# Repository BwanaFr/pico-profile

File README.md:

# pico-profile

This project goal is to emulate a Profile/Widget hard disk.
My ultimate goal is to be able to use this circuit with my Apple Lisa computer.

It's a work in progress and not yet ready for production.

## Demo
A short video showing the project in action is available on [Youtube](https://youtu.be/dQjzqoluw7A)

## Licensing
The final license of this project is not yet determined.
No commercial usage of this project can be made.

## TODO:
- Improve how Apple resets the MCU
- Add buttons to choose the disk image to use
- ~~Add more silkscreen information (power supply polarity...)~~
- Design a 3D printed enclosure
- ~~Fix the 74L280 footprint on PCB~~
- Make a through hole PCB version
- Test it with an Apple III

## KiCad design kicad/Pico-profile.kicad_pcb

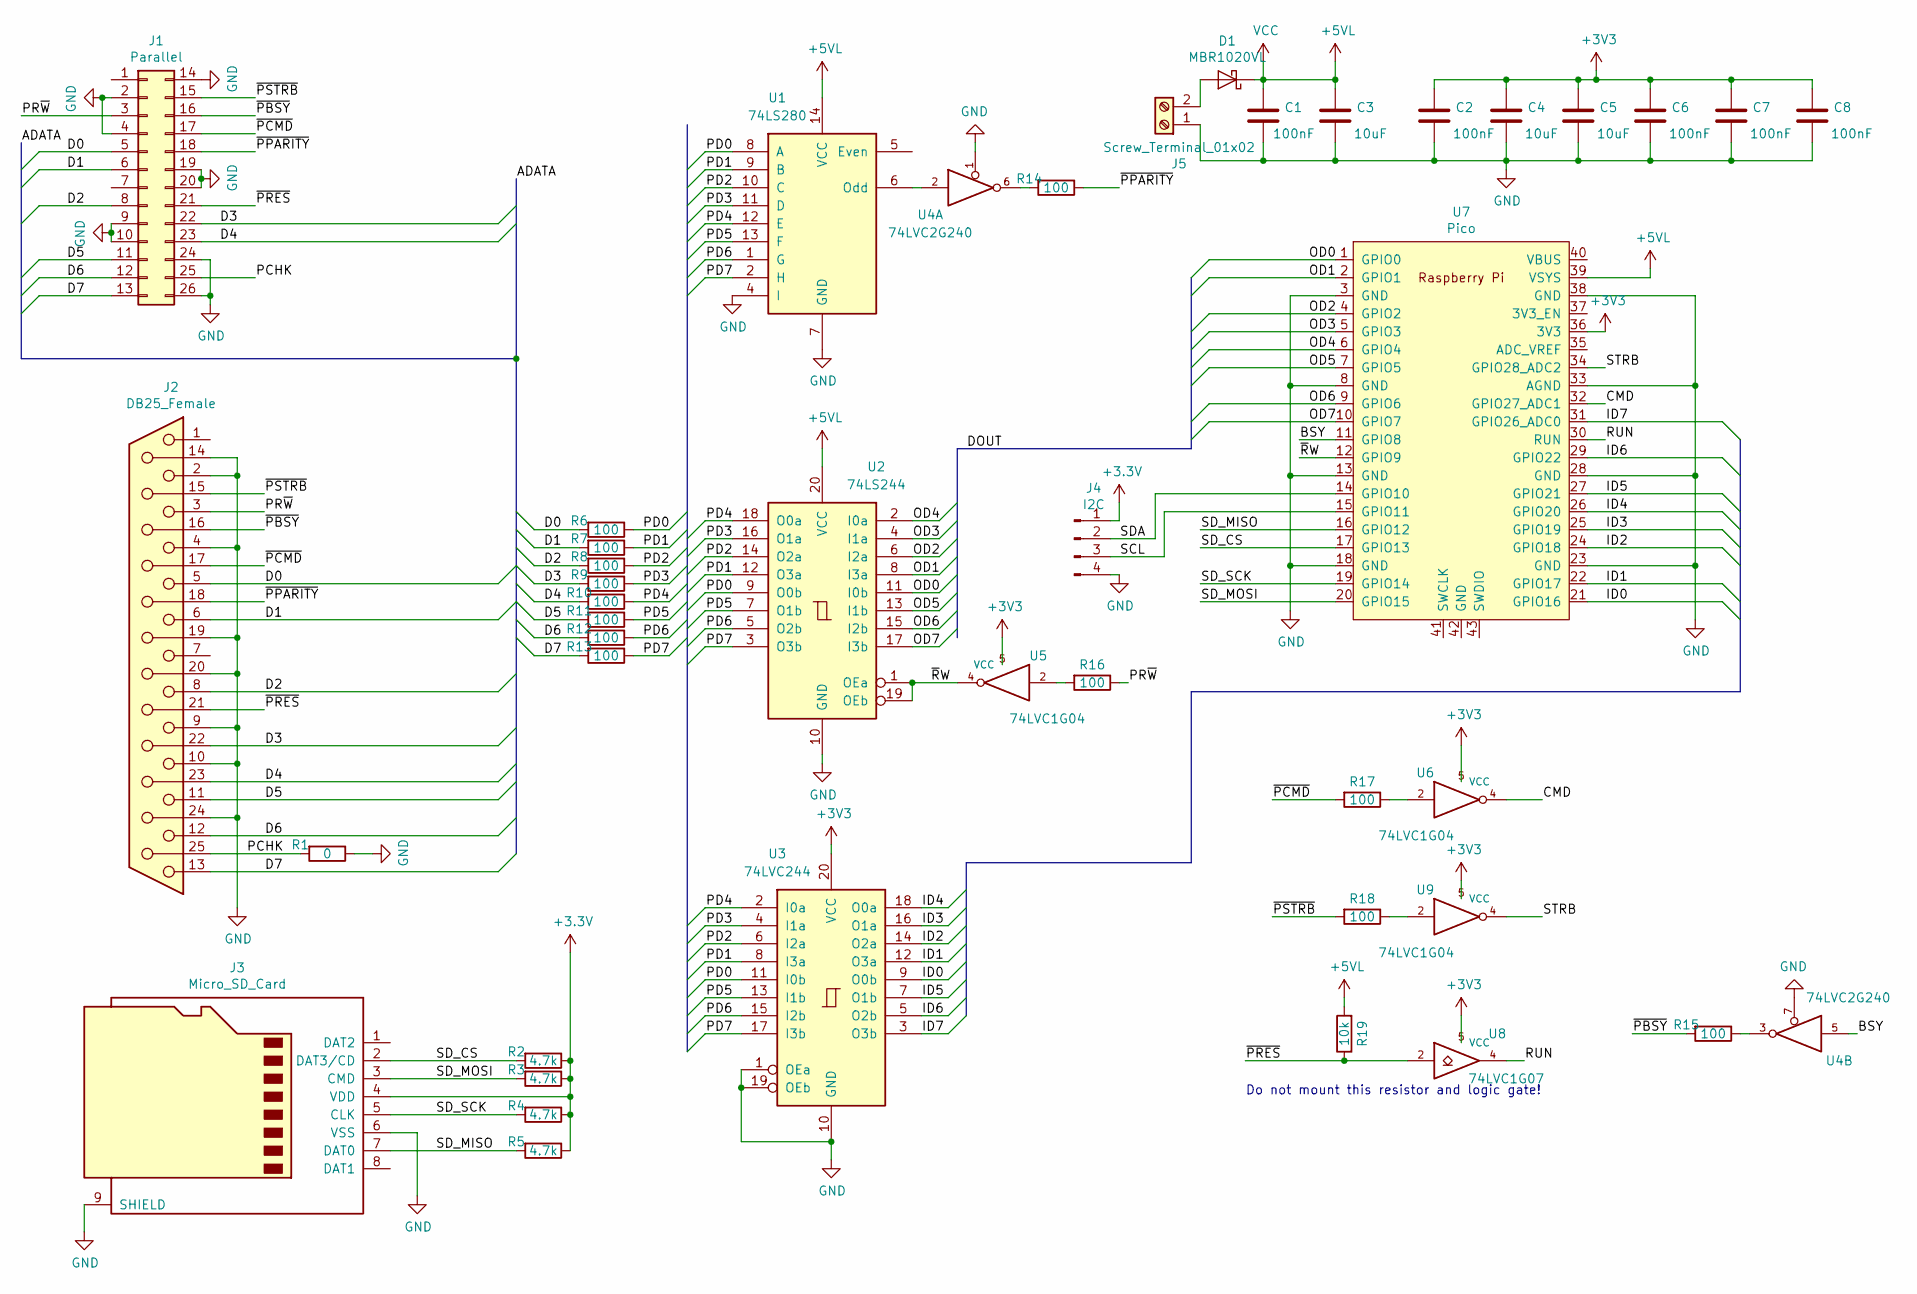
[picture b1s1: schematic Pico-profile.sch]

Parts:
C1, C2, C6, C7, C8: 100nF; C_0603_1608Metric
C3, C4, C5: 10uF; C_0603_1608Metric
D1: MBR1020VL; D_SOD-123F
J1: Parallel; IDC-Header_2x13_P2.54mm_Vertical
J2: DB25_Female; DSUB-25_Female_Horizontal_P2.77x2.84mm_EdgePinOffset7.70mm_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
J3: Micro_SD_Card; microSD_HC_Molex_104031-0811
J4: I2C; PinHeader_1x04_P2.54mm_Vertical
J5: Screw_Terminal_01x02; PhoenixContact_MSTBA_2,5_2-G-5,08_1x02_P5.08mm_Horizontal
R1: 0; R_0603_1608Metric
R2, R3, R4, R5: 4.7k; R_0603_1608Metric
R6, R7, R8, R9, R10, R11, R12, R13, R14, R15, R16, R17, R18: 100; R_0603_1608Metric
R19: 10k; R_0603_1608Metric
U1: 74LS280; SO-16_5.3x10.2mm_P1.27mm
U2: 74LS244; SOIC-20W_7.5x12.8mm_P1.27mm
U3: 74LVC244; SOIC-20W_7.5x12.8mm_P1.27mm
U4: 74LVC2G240; TSSOP-8_3x3mm_P0.65mm
U5, U6, U9: 74LVC1G04; SOT-23-5_HandSoldering
U7: Pico; RPi_Pico_SMD_TH
U8: 74LVC1G07; SOT-23-5_HandSoldering

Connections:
+5VL: C1.1, C3.1, D1.1 (K), R19.2, U1.14 (VCC), U2.20 (VCC), U4.8 (VCC), U7.39 (VSYS)
/BSY: U4.5, U7.11 (GPIO8)
/CMD: U6.4, U7.32 (GPIO27_ADC1)
/D0: J1.5, J2.5, R6.2
/D1: J1.6, J2.6, R7.2
/D2: J1.8, J2.8, R8.2
/D3: J1.22, J2.22, R9.2
/D4: J1.23, J2.23, R10.2
/D5: J1.11, J2.11, R11.2
/D6: J1.12, J2.12, R12.2
/D7: J1.13, J2.13, R13.2
/ID0: U3.9 (O0b), U7.21 (GPIO16)
/ID1: U3.12 (O3a), U7.22 (GPIO17)
/ID2: U3.14 (O2a), U7.24 (GPIO18)
/ID3: U3.16 (O1a), U7.25 (GPIO19)
/ID4: U3.18 (O0a), U7.26 (GPIO20)
/ID5: U3.7 (O1b), U7.27 (GPIO21)
/ID6: U3.5 (O2b), U7.29 (GPIO22)
/ID7: U3.3 (O3b), U7.31 (GPIO26_ADC0)
/OD0: U2.11 (I0b), U7.1 (GPIO0)
/OD1: U2.8 (I3a), U7.2 (GPIO1)
/OD2: U2.6 (I2a), U7.4 (GPIO2)
/OD3: U2.4 (I1a), U7.5 (GPIO3)
/OD4: U2.2 (I0a), U7.6 (GPIO4)
/OD5: U2.13 (I1b), U7.7 (GPIO5)
/OD6: U2.15 (I2b), U7.9 (GPIO6)
/OD7: U2.17 (I3b), U7.10 (GPIO7)
/PCHK: J1.25, J2.25, R1.2
/PD0: R6.1, U1.8 (A), U2.9 (O0b), U3.11 (I0b)
/PD1: R7.1, U1.9 (B), U2.12 (O3a), U3.8 (I3a)
/PD2: R8.1, U1.10 (C), U2.14 (O2a), U3.6 (I2a)
/PD3: R9.1, U1.11 (D), U2.16 (O1a), U3.4 (I1a)
/PD4: R10.1, U1.12 (E), U2.18 (O0a), U3.2 (I0a)
/PD5: R11.1, U1.13 (F), U2.7 (O1b), U3.13 (I1b)
/PD6: R12.1, U1.1 (G), U2.5 (O2b), U3.15 (I2b)
/PD7: R13.1, U1.2 (H), U2.3 (O3b), U3.17 (I3b)
/PR~W: J1.3, J2.3, R16.1
/RUN: U7.30 (RUN), U8.4
/SCL: J4.3, U7.15 (GPIO11)
/SDA: J4.2, U7.14 (GPIO10)
/SD_CS: J3.2 (DAT3/CD), R2.2, U7.17 (GPIO13)
/SD_MISO: J3.7 (DAT0), R5.2, U7.16 (GPIO12)
/SD_MOSI: J3.3 (CMD), R3.2, U7.20 (GPIO15)
/SD_SCK: J3.5 (CLK), R4.2, U7.19 (GPIO14)
/STRB: U7.34 (GPIO28_ADC2), U9.4
/~PBSY: J1.16, J2.16, R15.2
/~PCMD: J1.17, J2.17, R17.2
/~PPARITY: J1.18, J2.18, R14.1
/~PRES: J1.21, J2.21, R19.1, U8.2
/~PSTRB: J1.15, J2.15, R18.2
/~R~W: U2.1 (OEa), U2.19 (OEb), U5.4, U7.12 (GPIO9)
GND: C1.2, C2.2, C3.2, C4.2, C5.2, C6.2, C7.2, C8.2, J1.2, J1.4, J1.9, J1.10, J1.14, J1.19, J1.20, J1.24, J1.26, J2.2, J2.4, J2.9, J2.10, J2.14, J2.19, J2.20, J2.24, J3.6 (VSS), J3.9 (SHIELD), J4.4, J5.1, R1.1, U1.4 (I), U1.7 (GND), U2.10 (GND), U3.1 (OEa), U3.10 (GND), U3.19 (OEb), U4.1, U4.4 (GND), U4.7, U5.3 (GND), U6.3 (GND), U7.3 (GND), U7.8 (GND), U7.13 (GND), U7.18 (GND), U7.23 (GND), U7.28 (GND), U7.33 (AGND), U7.38 (GND), U8.3 (GND), U9.3 (GND)
unnamed: D1.2 (A), J5.2
unnamed: R14.2, U4.6
unnamed: R15.1, U4.3
unnamed: R16.2, U5.2
unnamed: R17.1, U6.2
unnamed: R18.1, U9.2
unnamed: U1.6 (Odd), U4.2

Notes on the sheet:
Do not mount this resistor and logic gate!

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
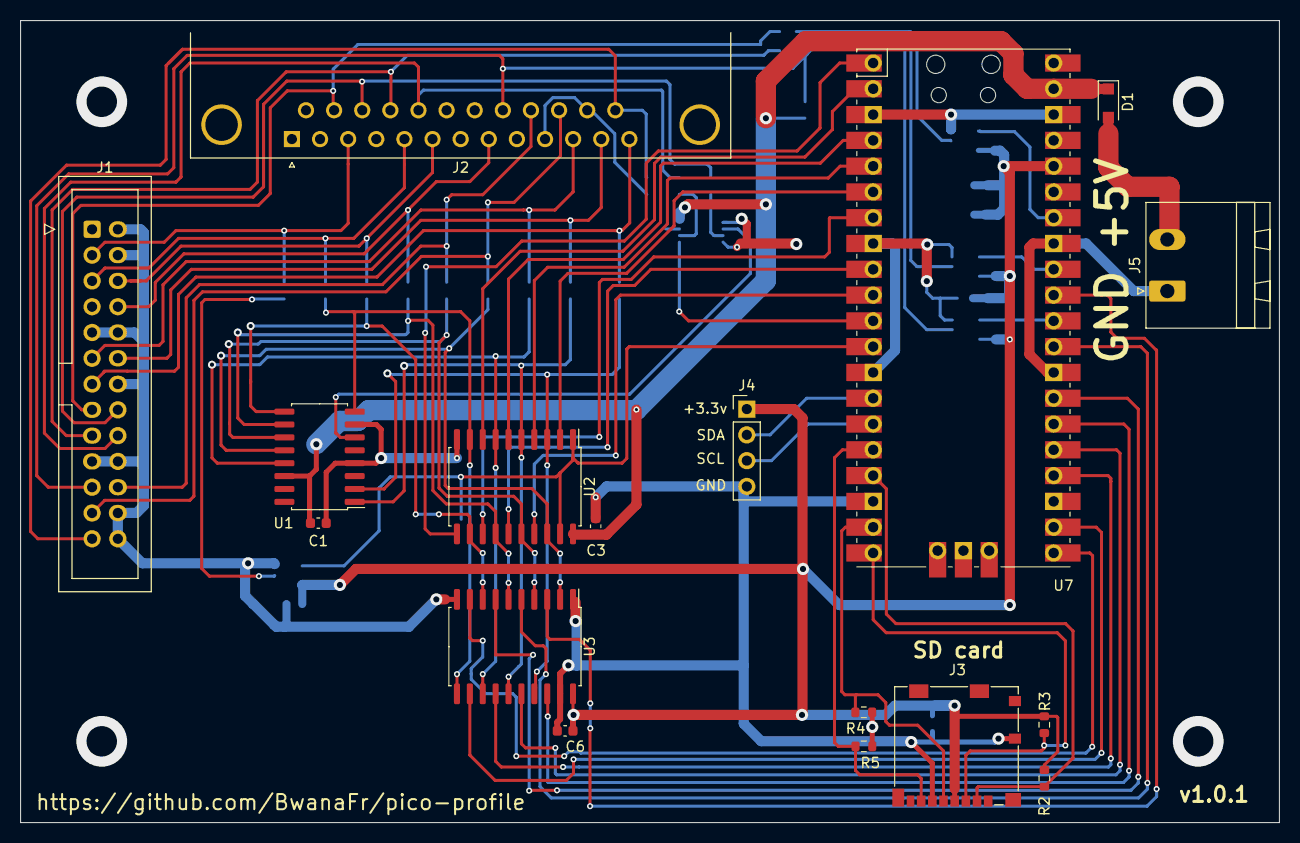
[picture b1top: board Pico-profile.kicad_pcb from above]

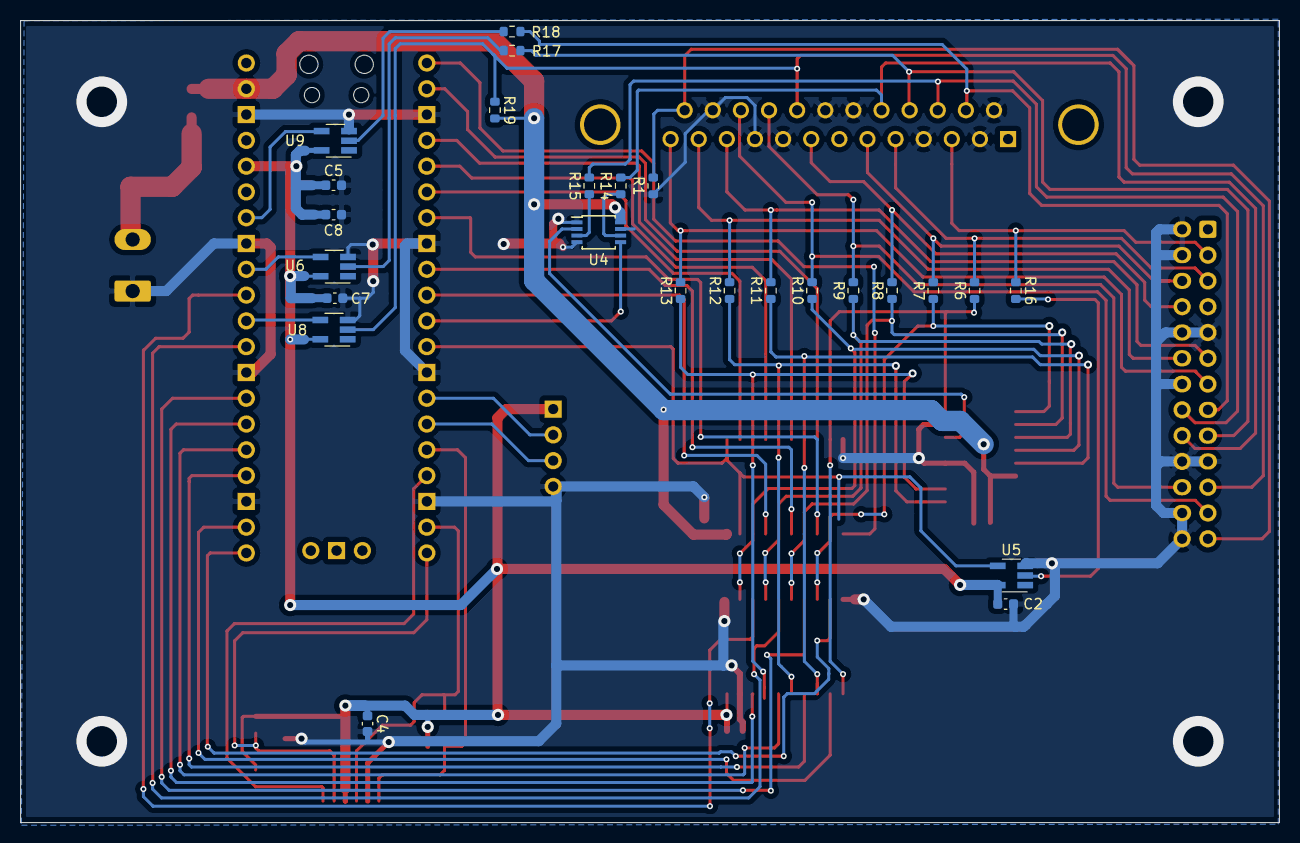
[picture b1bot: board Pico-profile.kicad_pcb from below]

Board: 2 copper layers, 124.0 x 79.0 mm, 42 parts (25 on the bottom side), 60 nets.

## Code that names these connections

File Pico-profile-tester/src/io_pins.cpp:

#include <Arduino.h>
#include "io_pins.h"

void configureIO()
{
    //Configure bus as input
    pinMode(PD0, INPUT);
    pinMode(PD1, INPUT);
    pinMode(PD2, INPUT);
    pinMode(PD3, INPUT);
    pinMode(PD4, INPUT);
    pinMode(PD5, INPUT);
    pinMode(PD6, INPUT);
    //Strobe is an input on profile side
    pinMode(PSTRB, OUTPUT);
    //Busy is from profile to this
    pinMode(PBSY, INPUT);
    //Command is from this to profile
    pinMode(PCMD, OUTPUT);
    //Parity is from profile to this
    pinMode(PPARITY, INPUT);
    //Read/write is from this to profile
    pinMode(PRW, OUTPUT);
    //Reset is from this to profile
    pinMode(RESET, OUTPUT);
    //LED for tests
    pinMode(LED_BUILTIN, OUTPUT);

    //Set direction as read
    digitalWrite(PRW, 0);
    //Don't reset the pico
    digitalWrite(RESET, 1);
    //No commands yet
    digitalWrite(PCMD, 1);
    //Keep strobe high
    digitalWrite(PSTRB, 1);
}

void setPortDir(bool output, uint8_t outValue = 0)
{
    if(output)
    {
        uint8_t oldSREG = SREG;
        cli();
        //Write output
        PORT10 = (PORT10 & B11111100) | (outValue & B00000011);
        PORT27 = (PORT27 & B00000011) | (outValue & B11111100);
        //Sets DDR
        DDR10 |= B00000011;
        DDR27 |= B11111100;
        SREG = oldSREG;
    }else{
        uint8_t oldSREG = SREG;
        cli();
        //Sets DDR
        PORT10 &= ~B00000011;
        PORT27 &= ~B11111100;
        DDR10 &= ~B00000011;
        DDR27 &= ~B11111100;
        SREG = oldSREG;
    }
}

uint8_t readBus()
{
    return (PIN10 & B00000011) | (PIN27 & B11111100);
}

void cycleStrobe()
{
    //Signal data-taken
    digitalWrite(PSTRB, false);    
    digitalWrite(PSTRB, true);
}

uint8_t readData(bool useStrobe)
{
    //Set direction as read
    digitalWrite(PRW, 1);
    //Set port direction to read
    setPortDir(false);
    
    uint8_t value = readBus();
    if(useStrobe){
        cycleStrobe();
    }    
    return value;
}

uint8_t readDataParity(bool& parity, bool useStrobe)
{
    //Set direction as read
    digitalWrite(PRW, 1);
    //Set port direction to read
    setPortDir(false);
    
    uint8_t value = readBus();
    parity = digitalRead(PPARITY);
    if(useStrobe){
        //Signal data-taken
        cycleStrobe();
    }    
    return value;
}

void writeData(uint8_t data, bool useStrobe)
{
    //Set port as output
    setPortDir(true, data);    
    //Set direction as write
    digitalWrite(PRW, 0);
    if(useStrobe){
        cycleStrobe();
    }
}

bool checkParity(uint8_t data)
{
    bool parity = digitalRead(PPARITY);
    int count = 0;
    for(int i=0;i<8;++i){
        if((data>>i) & 0x1){
            ++count;
        }
    }
    bool even = ((count % 2) == 0);
    return even == parity;
}

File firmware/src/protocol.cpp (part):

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    modify |= 1u << OD5_PIN;
    modify |= 1u << OD6_PIN;
    modify |= 1u << OD7_PIN;
    modify |= 1u << BSY_PIN;
    modify |= 1u << RW_PIN;
    modify |= 1u << ID0_PIN;
    modify |= 1u << ID1_PIN;
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    modify |= 1u << ID5_PIN;
    modify |= 1u << ID6_PIN;
    modify |= 1u << ID7_PIN;
    modify |= 1u << CMD_PIN;
    modify |= 1u << STRB_PIN;
    
    dir |= 1u << OD0_PIN;
    dir |= 1u << OD1_PIN;
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    dir |= 1u << OD5_PIN;
    dir |= 1u << OD6_PIN;
    dir |= 1u << OD7_PIN;
    dir |= 1u << BSY_PIN;
    //Init GPIO
    for(uint32_t i=0;i<32;++i){
        if((modify>>i) & 0x1){
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    pioDataReadCfg_ = pico_profile_data_read_program_get_default_config(pioDataReadOffs_);
    sm_config_set_out_pins(&pioDataReadCfg_, 0, 8);                 //8 outputs
    sm_config_set_out_shift(&pioDataReadCfg_, true, true, 8);       //Shift right, autopull of 8 bits
    sm_config_set_in_pins(&pioDataReadCfg_, ID0_PIN);               //Input starting at ID0_PIN (GPIO16)
    sm_config_set_in_shift(&pioDataReadCfg_, false, true, 11);      //Shift right, autopull of 11 bits (to take into account GPIO 26)
    sm_config_set_jmp_pin(&pioDataReadCfg_, RW_PIN);                //Use R/W as jump pin

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    pioDataWriteCfg_ = pico_profile_data_write_program_get_default_config(pioDataWriteOffs_);
    sm_config_set_out_pins(&pioDataWriteCfg_, 0, 8);                 //8 outputs
    sm_config_set_out_shift(&pioDataWriteCfg_, true, true, 8);       //Shift right, autopull of 8 bits
    sm_config_set_in_pins(&pioDataWriteCfg_, ID0_PIN);               //Input starting at ID0_PIN (GPIO16)
    sm_config_set_in_shift(&pioDataWriteCfg_, false, true, 11);      //Shift right, autopull of 11 bits (to take into account GPIO 26)
    sm_config_set_jmp_pin(&pioDataWriteCfg_, RW_PIN);                //Use R/W as jump pin

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    pioCmdCfg_ = pico_profile_cmd_program_get_default_config(pioCmdOffs_);
    sm_config_set_out_pins(&pioCmdCfg_, 0, 8);                  //8 outputs
    sm_config_set_out_shift(&pioCmdCfg_, true, true, 8);        //Shift right, autopull of 8 bits
    sm_config_set_sideset_pins(&pioCmdCfg_, BSY_PIN);           //Busy pin (side-set) is GPIO8
    sm_config_set_in_pins(&pioCmdCfg_, ID0_PIN);                //Input starting at GPIO16
    sm_config_set_in_shift(&pioCmdCfg_, false, true, 11);       //Shift right, autopull of 11 bits (to take into account GPIO 26)

    pio_sm_init(CMD_PIO, CMD_SM, pioCmdOffs_, &pioCmdCfg_);    //Initialize state machine
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
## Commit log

2021-08-17 Initial commit. Still in development
2021-08-25 Intermediate commit. Worked on hardware
2021-08-26 Hardware first revision. Need cosmetic changes
2021-08-27 Cosmetic changes on PCB
2021-08-27 Moved custom libs to project
2021-08-27 Fixed wrong lib path
2021-08-27 Added gerbers for prototype production
2021-10-19 Test of SD card ok
2021-10-22 Started implementing the tester
2021-10-26 Still playing with PIO
2021-10-27 Started to implement DC42 file handling
2021-11-04 Updated FatFS to 1.4b. Continued implementation
2021-11-05 First try on real hardware. Work still needed
2021-11-05 Timeouts in read/write
2021-11-08 Moved to DMA
2021-11-09 Removed printf
2021-11-09 Changed PIO:
2021-11-10 Fixed the read state machine
2021-11-11 First version working with real Lisa.
2021-11-11 No VSCodium workspace here!
2021-11-12 Fixed GCC compilation warning
2021-11-15 Change way commands are handled
2021-11-15 New way to handle command. Make this more dumb
2021-11-15 Added dedicated buffer for command
2021-11-16 Reworked state machines for handling unexpected commands
2021-11-18 Playing with OLED display
2021-11-22 OLED display implementation
2021-11-23 Stack overflow, moved DC42File and Protocol instances as static
2021-11-25 OLED display working.
2021-11-25 Fixed minor display issues
2021-11-26 Added configuration file proto
2021-11-30 Added configuration file. Not really optimized
2021-12-02 Configuration file using templates
2021-12-03 Fully implemented configuration file
2021-12-03 Add CI
    Adds CI for GitHub
2021-12-05 Added release.zip in firmware
2021-12-06 Updated release.yml
2021-12-06 Added version in logo
2021-12-17 Fixed PCB footprint. Added more silkscreen information.
